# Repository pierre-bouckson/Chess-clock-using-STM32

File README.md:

# Chess Clock using STM32

A fully functional chess clock built with an STM32 microcontroller, using hardware timers and external components for a realistic, competitive experience. This project combines embedded programming, electronics, and 3D printing.

---

## Required Equipment

1. **STM32F072RB** microcontroller (or any STM32 with hardware timers)
2. **3D-printed enclosure**
3. **5V power supply** (via USB power bank)
4. **4 screws** (for enclosure assembly)
5. **Shaft** – 3.5mm diameter, 6cm long
6. **4 magnets**
7. **8-digit 7-segment display**  
   [TDSG3160-M – Vishay](https://fr.farnell.com/vishay/tdsg3160-m/7-seg-display-com-cathode-grn/dp/3777869)
8. **2 LED display drivers**  
   [MAX6958AAEE – Analog Devices](https://fr.farnell.com/analog-devices/max6958aaee/driver-afficheur-led-40-a-125/dp/2516031)
9. **Passive components**: resistors, capacitors, tactile button, etc.

---

## Tools Used

- [KiCad](https://kicad.org/) – for PCB design
- [STM32CubeIDE](https://www.st.com/en/development-tools/stm32cubeide.html) – for firmware development

---

## Project Overview

The chess clock is powered by an **STM32F072RB**, using two hardware timers (TIM6 and TIM7) to track each player's countdown in real time. Turn switching is handled by a physical mechanism using a rotating shaft and magnets. Two **MAX6958** drivers control the 7-segment displays. The clock supports multiple time modes and optional time increments.

---

## Assembly Guide

### 1. Print the Enclosure

- Insert magnets into the 4 dedicated holes.
- Create a custom push-button using aluminum (as shown below):

- Connect the button between **5V** and **PB0**.
- Drill a hole in the enclosure to pass the power cable.

### 2. Prepare the Electronics

- Use **4 pull-up resistors** (1kΩ) for I2C communication.
- Use **9 resistors** (330Ω) for the LED segments.
- Connect the first display driver to:  
  - 3.3V, GND  
  - PB8 (SCL), PB9 (SDA)

- Connect the second driver to:  
  - 3.3V, GND  
  - PB10 (SCL), PB11 (SDA)

> Don't forget to add **decoupling capacitors** near the power pins.

---

## Repository Structure

- `3D_model/` – 3D-printable enclosure files (STL)
- `software_STM32/` – STM32 firmware (C)
- `Image/` – Photos
- `hardware_kicad/` – Schematics and PCB files
- `README.md` – This file

---

Feel free to clone the repository, give feedback, or open issues!

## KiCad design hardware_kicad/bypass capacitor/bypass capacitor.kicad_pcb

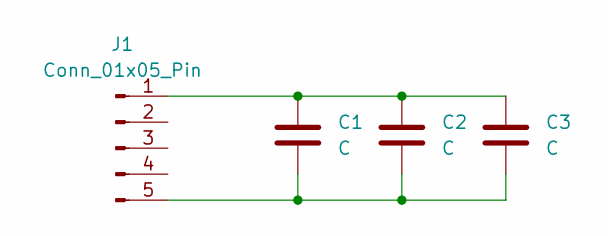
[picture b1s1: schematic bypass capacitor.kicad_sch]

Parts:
C1: C; C_Disc_D5.1mm_W3.2mm_P5.00mm
C2: C; C_Rect_L9.0mm_W2.5mm_P7.50mm_MKT
C3: C; CP_Radial_D8.0mm_P3.50mm
J1: Conn_01x05_Pin; PinHeader_1x05_P2.54mm_Vertical

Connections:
unnamed: C1.1, C2.1, C3.1, J1.1
unnamed: C1.2, C2.2, C3.2, J1.5

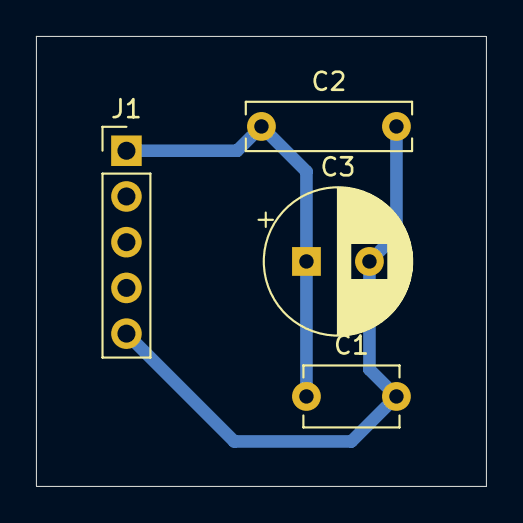
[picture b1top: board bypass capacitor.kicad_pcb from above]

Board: 2 copper layers, 25.0 x 25.0 mm, 4 parts (0 on the bottom side), 2 nets.

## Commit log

2025-05-05 Update 05/05/25
2025-05-05 Remove .metadata
